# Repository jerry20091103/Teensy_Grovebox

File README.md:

# Teensy Grovebox

- An all-in-one music multi-tool in a 25-key MIDI keyboard form factor.
- Made with Teensy 4.1 and Teensy Audio Board.
- [Demo video for the synth function.](https://www.youtube.com/watch?v=64bXlY2FwMQ)
- [Demo video for the Sampler function.](https://youtu.be/v5BAqmPcjrQ)
## Hardware Features
- 25-key MIDI keyboard with mechanical key switches.
- 4 encoder knobs and a joystick.
- 3.5 inch TFT touch screen.
- Built-in audio interface with stereo line input/output, and headphone output.
- Onboard speaker and microphone.
- 10+ hours of battery life.
- USB-C charging and data transfer.
- Supports sustain pedal.
- Exposed I2C and S/PDIF headers.
- ...

## Software Features
- USB MIDI keyboard with pitchbend, mod wheel, and 4 assignable knobs.
- Wavetable synth mode to play SF2 soundfonts. (with Teensy SoundFont Decoder ...link)
- Polyphonic synth engine with 8 voices, each with 2 oscillators, 2 LFOs, 3 envelopes, and 1 filter.
- Sampler mode.
- Effects like delay, chorus, reverb... (under development).

## Folders in this repo
> There's a readme file in each folder with more details.
- `Teensy_Grovebox_Hardware`
    - Kicad files for schematic and PCB. 
    - 3D files for the case.
- `Teensy_Grovebox_CODE`
    - Arduino code for the Teensy 4.1.
    - Uses PlatformIO.
- `Joystick_Board`
    - Kicad schematic and PCB files for the joystick board used in the Teensy Grovebox.

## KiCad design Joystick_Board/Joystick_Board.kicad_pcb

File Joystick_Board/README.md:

# Joystick Board

## Overview
- This is a simple joystick board that takes standard ALPS joystick modules. (like the ones in PlayStation and Xbox controllers)
- The overall thickness of the Teensy Grovebox would be too thick if the joystick module was mounted on the main PCB. So the joystick board is a separate board that connects to the Teensy Grovebox PCB.
## Contents
- Kicad files and Gerber outputs for the joystick board.

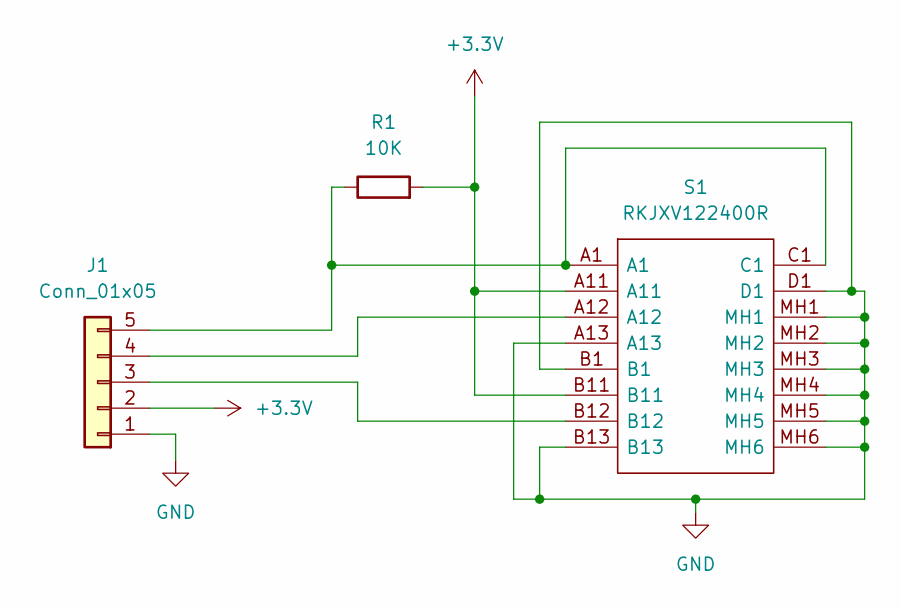
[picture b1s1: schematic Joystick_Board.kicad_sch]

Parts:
J1: Conn_01x05; PinHeader_1x05_P2.54mm_Vertical
R1: 10K; R_1206_3216Metric_Pad1.30x1.75mm_HandSolder
S1: RKJXV122400R; Mouser Part Number 688-RKJXV122400R

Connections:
+3V3: J1.2, R1.2, S1.A11, S1.B11
GND: J1.1, S1.A13, S1.B1, S1.B13, S1.D1, S1.MH1, S1.MH2, S1.MH3, S1.MH4, S1.MH5, S1.MH6
unnamed: J1.3, S1.B12
unnamed: J1.4, S1.A12
unnamed: J1.5, R1.1, S1.A1, S1.C1

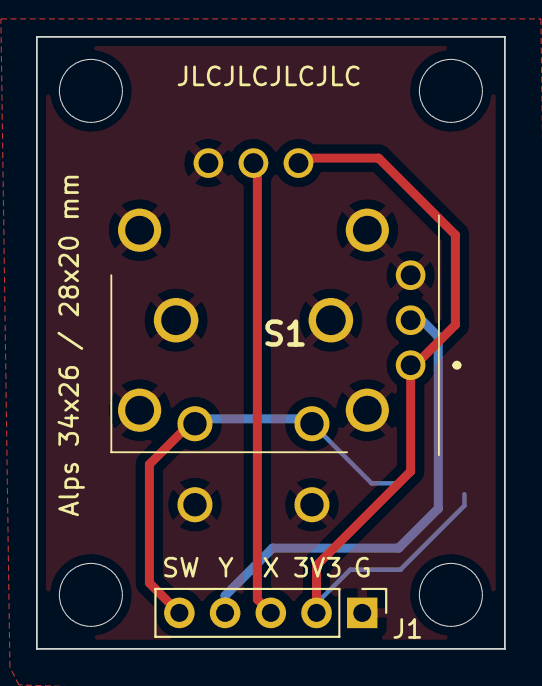
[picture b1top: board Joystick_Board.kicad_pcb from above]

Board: 2 copper layers, 26.0 x 34.0 mm, 4 parts (1 on the bottom side), 5 nets.

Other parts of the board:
U4: HOLE; MountingHole

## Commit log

2022-04-29 Finished MIDI feature.
2022-05-01 Add power off prompt. Fix bugs in Midi page.
2022-05-12 Finished AudioIO.
2022-05-16 Add home page.
2022-05-17 Finished voice pool and basic waveTable synth.
2022-05-19 Refactor level meter code.
2022-05-19 Fix typo in AudiooutPage.
2022-06-02 Add velocity detection with microphone.
2022-06-02 Create Audio folder.
2022-06-02 Change includes for new Audio folder.
2022-06-02 Add master volume for waveTable; some refactoring.
2022-06-02 Add AudioFX class and reverb FX.
2022-06-02 Add more args for getCurPage, to access input callbacks when in popup.
2022-06-28 Add sf2 select list box.
2022-06-28 Add lvgl library.
2022-06-28 Add lvgl log.
2022-06-30 Successful compile with lvgl; ported MidiPage.
2022-07-01 Ported HomePage.
2022-07-01 Add stack navigation.
2022-07-02 Reduce RAM1 use; finish audio input UI objects.
2022-07-03 Finished audio input tab object layout.
2022-07-04 Finished output mixer UI objects.
2022-07-07 Finished basic AudioPage.
2022-07-08 Finished basic WaveTablePage.
2022-07-08 Add sound font switching.
2022-07-09 Add piano sound font.
2022-07-11 PCB bug fix.
2022-07-11 Add synth voice and SynthPage
2022-07-11 Increase lvgl memory size; add lvgl memory monitor
2022-07-15 Add osc1, osc2 to synth.
2022-07-17 Add amplitude envelope to synth.
2022-07-21 Remove leftover RMS sturff.
2022-07-21 Add setUserData() in all pages.
2022-07-21 Add noise generator in synth.
2022-07-29 Add ladder filter to synth
2022-08-03 Add modified teensy audio gui tool to the repo.
2022-08-16 Add modulation matrix system to Synth.
2022-08-17 Fix bug: pitchbend fails when osc is modulated.
2022-12-19 Folder organization.
2022-12-20 Add basic README.md.
2022-12-20 Add images to readmes.
2022-12-23 Fix typos in readmes.
2023-01-11 Include 5v booster model number in PCB files.
2023-01-11 Add video link in readme.
2023-01-31 Rewrite synth modulation system for cleaner code.
2023-01-31 Remove debug messages in AudioSynth.
2023-01-31 Bug fix in AudioSynth. Turn off OSCs when not in synth mode.
2023-02-01 Upgrade LVGL library to 8.3.4
2023-02-01 Move lvgl_buf to DMAMEM.
2023-02-01 Upgrade ILI9341_T4 library to version 1.5.3.
2023-02-01 Envelopes share same GUI objects in SynthPage.
2023-02-02 Fix bugs in AudioSynth.
2023-02-02 OSCs share the same GUI objects in SynthPage.
2023-02-03 Add clip / playClip audio objects.
2023-02-03 Half done SampleEditorPage.
2023-02-03 Update Gui_CreateButton()
2023-02-04 Finished SampleEditorPage.
2023-02-04 Change peakLed implementation. (lv_led -> lv_obj)
2023-02-04 Add loop crossfade and level meter / polish, in SampleEditorPage.
2023-02-05 Add Gui_Spinbox. Replace multiple objects with spinbox.
2023-02-05 Update Gui_Button.
2023-02-08 Finished sampler function in AudioSynth.
2023-02-12 Found bugs in pitchbend of wavetable synth mode.
2023-02-28 Finished basic Sampler UI.
2023-02-28 Create valueText inside paramArc creator; new get value/title/unitText for paramArc.
2023-03-01 Add root key selection in sampler.
2023-03-04 Fix wrong title in envelope arc.
2023-03-04 Reduce touch input jitter.
2023-03-05 Remove biquad in sampler; minor update in UI.
2023-03-05 Add basic pitchbend to sampler.
2023-04-09 Add drumkit for demoing
2023-04-09 Update readme.
2023-05-07 Update hardware readme about the psram chips.
2023-06-03 Create LICENSE
2023-07-11 Add ClipLevel to a modulation capable parameter
2024-01-18 Add debugger support (not working properly)
2024-01-18 Add new GUI objects to replace old code.
2024-01-18 Port new dynamic memory GUI for MidiPage. Also port some objectes in SynthPage.
2024-01-19 Remove SerialPrint utility. USB debugging with USB dual serial works now. (MIDI and USB audio unavailable with debugging)
2024-01-19 Fix ccArc not set to NULL after delete
2024-01-20 Stop program at startup when debugging
2024-01-20 Remove serial prints; fix include error in AudioUtility; remove useless code.
2024-01-20 Add new VolumeBar GUI object.
2024-01-20 Port WaveTablePage to new dynamic memory GUI
2024-01-21 Fix bugs in Buttons and VolumeBar
2024-01-21 Add new Slider GUI object
2024-01-21 Port SampleEditorPage to new dynamic GUI.
2024-01-21 Move some functions to PROGMEM to save ram space.
2024-01-22 Use lv_obj_clean instead of delete; remove unused code; Move waveform points to DMAMEM.
2024-02-06 Fix bug in Button. Hold callback does not handle reverse checked state correctly.
2024-02-06 Fix bug in EnvelopeGraph. object width and height does not calculate during page load.
2024-02-06 Add support for non zero starting value for ParamArc. The offset is handled automatically. Also Add checks before calling from binded encoders.
2024-02-06 Add new SubPage system. Ported SynthPage to the new dynamic memory GUI.
2024-02-08 Add new "extraSmall" font
2024-02-08 New ParamArcMini object
2024-02-08 Ported AudioPage to new dynamic GUI.
2024-02-08 Add nullptr to pointer init.
2024-02-08 Refactor page classes and remove unused setUserData() functions
2024-02-08 Remove unnecessary code and update configurePage in Pages.cpp and WaveTablePage.cpp
2024-02-08 Reduce LV_MEM_SIZE in lv_conf.h from 128k to 64k
2024-02-09 Reduce LV_MEM_SIZE in lv_conf.h from 64k to 48k. Fix not unloading in loadAll(). Minor fix in AudioPage.
2024-02-10 Move modList from the audio system to GUI. Modulation subpage now loads mod entries correctly.
2024-02-29 Move octave fn button binding to its subpage.
2024-03-17 Finished saving current user data to micro SD card.
2024-03-30 Add UI at status bar for preset selection.
2024-05-12 Finished preset saving function with preset naming.
2024-05-12 Add "preset modified" indicator; make WaveTablePage support presets.
2024-05-25 Make SynthPage support presets.
